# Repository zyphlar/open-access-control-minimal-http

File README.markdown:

Open Access Control - HTTP Minimal Edition
======================================
AKA Open Access Control Interlock
---------------------------------

This is a stripped-down version of the 23b hackerspace's Open Access Control system, intended for embedded use with an RFID reader and Ethernet shield for authenticating Wiegand RFID cards with a webservice. Please see http://code.google.com/p/open-access-control/ for the main/full version.

For more info, contact @willbradley on Twitter.

Structure
---------

* This folder
  * Open Access Control folder
    * Open Access Control.ino (Arduino code -- open from the Arduino IDE.)
  * libraries folder (copy the contents of this folder to your Arduino program's libraries folder and restart the Arduino program.)
    * ShiftLCD folder
      * keywords.txt
      * ShiftLCD.cpp
      * ShiftLCD.h
    * PCATTACH folder
      * keywords.txt
      * PCATTACH.cpp
      * PCATTACH.h
    * Wiegand26 folder
      * keywords.txt
      * WIEGAND26.cpp
      * WIEGAND26.h
  * hardware folder
    * open-access-interlock.brd

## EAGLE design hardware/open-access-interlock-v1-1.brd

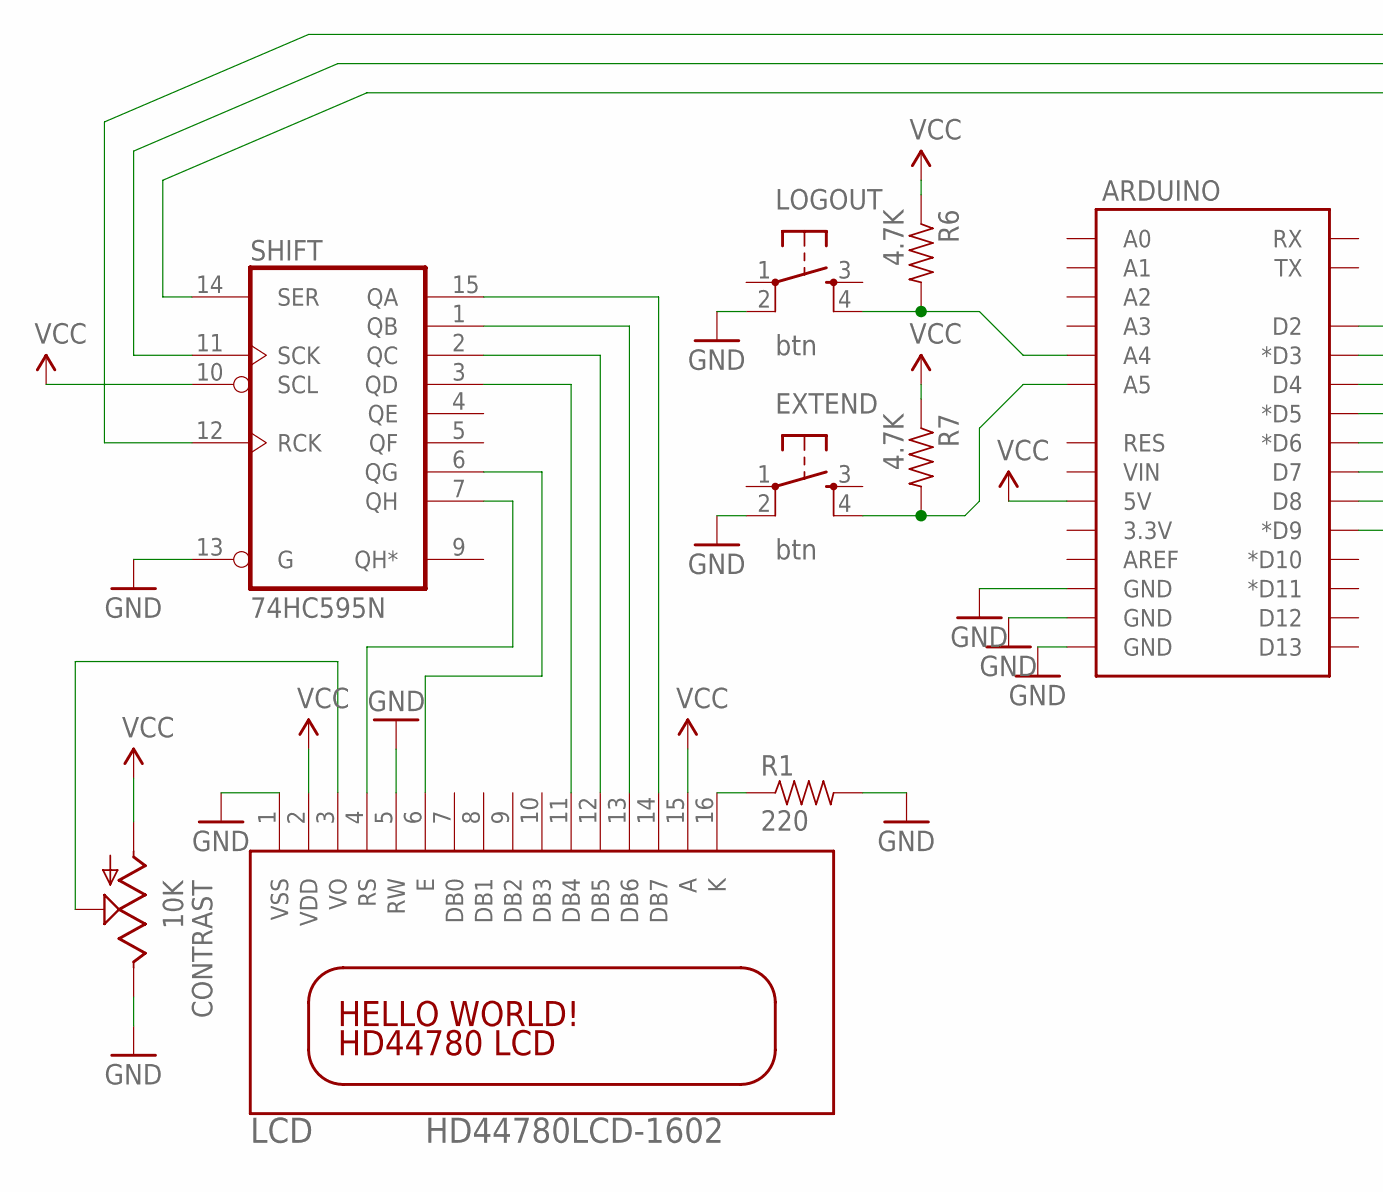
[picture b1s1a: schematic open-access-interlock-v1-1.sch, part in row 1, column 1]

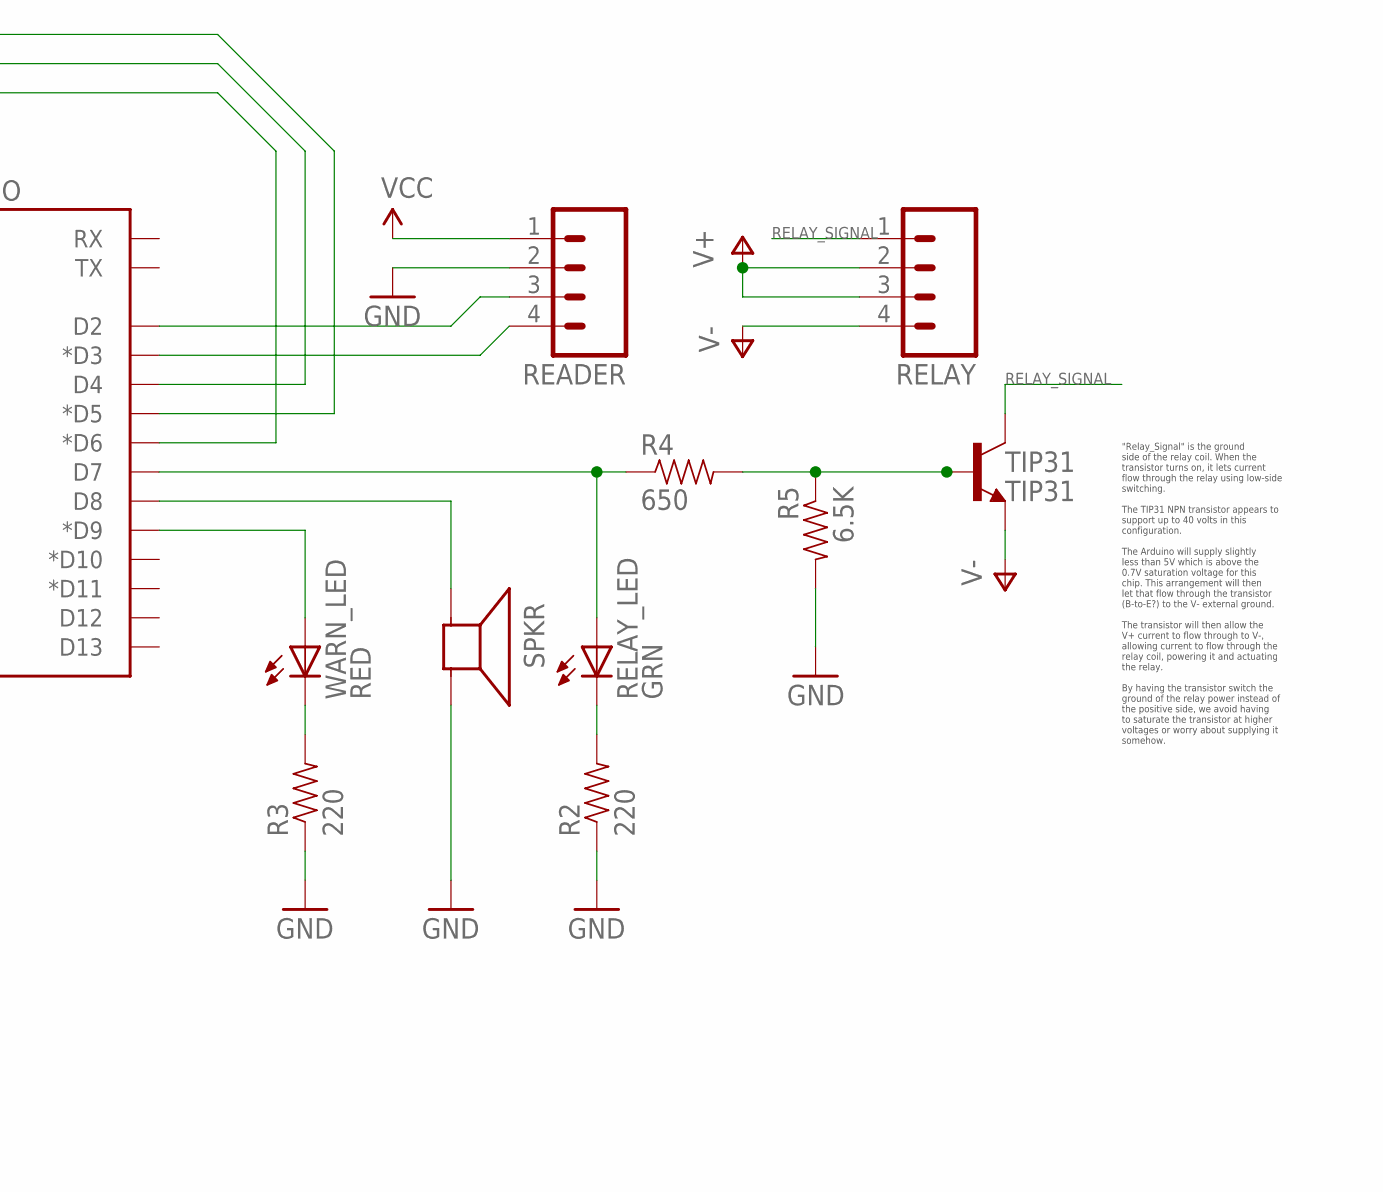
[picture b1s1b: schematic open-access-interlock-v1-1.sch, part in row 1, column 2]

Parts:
ARDUINO: ARDUINO_SHIELDNO_SILK; DUEMILANOVE_VIAS
CONTRAST: 10K; RS3
EXTEND: btn; TACTILE-PTH
LCD: HD44780LCD-1602; LCD1602
LOGOUT: btn; TACTILE-PTH
R1, R2, R3: 220; AXIAL-0.3
R4: 650; AXIAL-0.3
R5: 6.5K; AXIAL-0.3
R6, R7: 4.7K; AXIAL-0.3
READER: M04SCREW; SCREWTERMINAL-3.5MM-4
RELAY: M04SCREW; SCREWTERMINAL-3.5MM-4
RELAY_LED: GRN; LED5MM
SHIFT: 74HC595N; DIL16
SPKR: SPEAKER/PS12; PS12
TIP31: TIP31; TO220
WARN_LED: RED; LED5MM

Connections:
GND: ARDUINO.GND@0 (GND), ARDUINO.GND@1 (GND), ARDUINO.GND@2 (GND), CONTRAST.E, EXTEND.2, LCD.1 (VSS), LCD.5 (RW), LOGOUT.2, R1.P$2 (2), R2.P$1 (1), R3.P$1 (1), R5.P$2 (2), READER.2, SHIFT.8 (GND), SHIFT.13 (G), SPKR.P$2 (-)
unnamed: ARDUINO.D2, READER.3
unnamed: ARDUINO.D3 (*D3), READER.4
unnamed: LCD.13 (DB6), SHIFT.1 (QB)
unnamed: LCD.12 (DB5), SHIFT.2 (QC)
unnamed: ARDUINO.D6 (*D6), SHIFT.14 (SER)
unnamed: ARDUINO.D5 (*D5), SHIFT.12 (RCK)
unnamed: ARDUINO.D4, SHIFT.11 (SCK)
unnamed: ARDUINO.D7, R4.P$1 (1), RELAY_LED.A
unnamed: ARDUINO.D9 (*D9), WARN_LED.A
unnamed: ARDUINO.D8, SPKR.P$1 (+)
unnamed: LCD.6 (E), SHIFT.6 (QG)
unnamed: LCD.11 (DB4), SHIFT.3 (QD)
unnamed: ARDUINO.A4, LOGOUT.4, R6.P$2 (2)
unnamed: ARDUINO.A5, EXTEND.4, R7.P$2 (2)
unnamed: R2.P$2 (2), RELAY_LED.K (C)
unnamed: LCD.4 (RS), SHIFT.7 (QH)
unnamed: CONTRAST.S, LCD.3 (VO)
unnamed: LCD.16 (K), R1.P$1 (1)
unnamed: LCD.14 (DB7), SHIFT.15 (QA)
unnamed: R4.P$2 (2), R5.P$1 (1), TIP31.1 (B)
unnamed: R3.P$2 (2), WARN_LED.K (C)
RELAY_SIGNAL: RELAY.1, TIP31.2 (C)
V+: RELAY.2, RELAY.3
V-: RELAY.4, TIP31.3 (E)
VCC: ARDUINO.5V, CONTRAST.A, LCD.2 (VDD), LCD.15 (A), R6.P$1 (1), R7.P$1 (1), READER.1, SHIFT.10 (SCL), SHIFT.16 (VCC)

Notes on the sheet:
"Relay_Signal" is the ground side of the relay coil. When the transistor turns on, it lets current flow through the relay using low-side switching. The TIP31 NPN transistor appears to support up to 40 volts in this configuration. The Arduino will supply slightly less than 5V which is above the 0.7V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

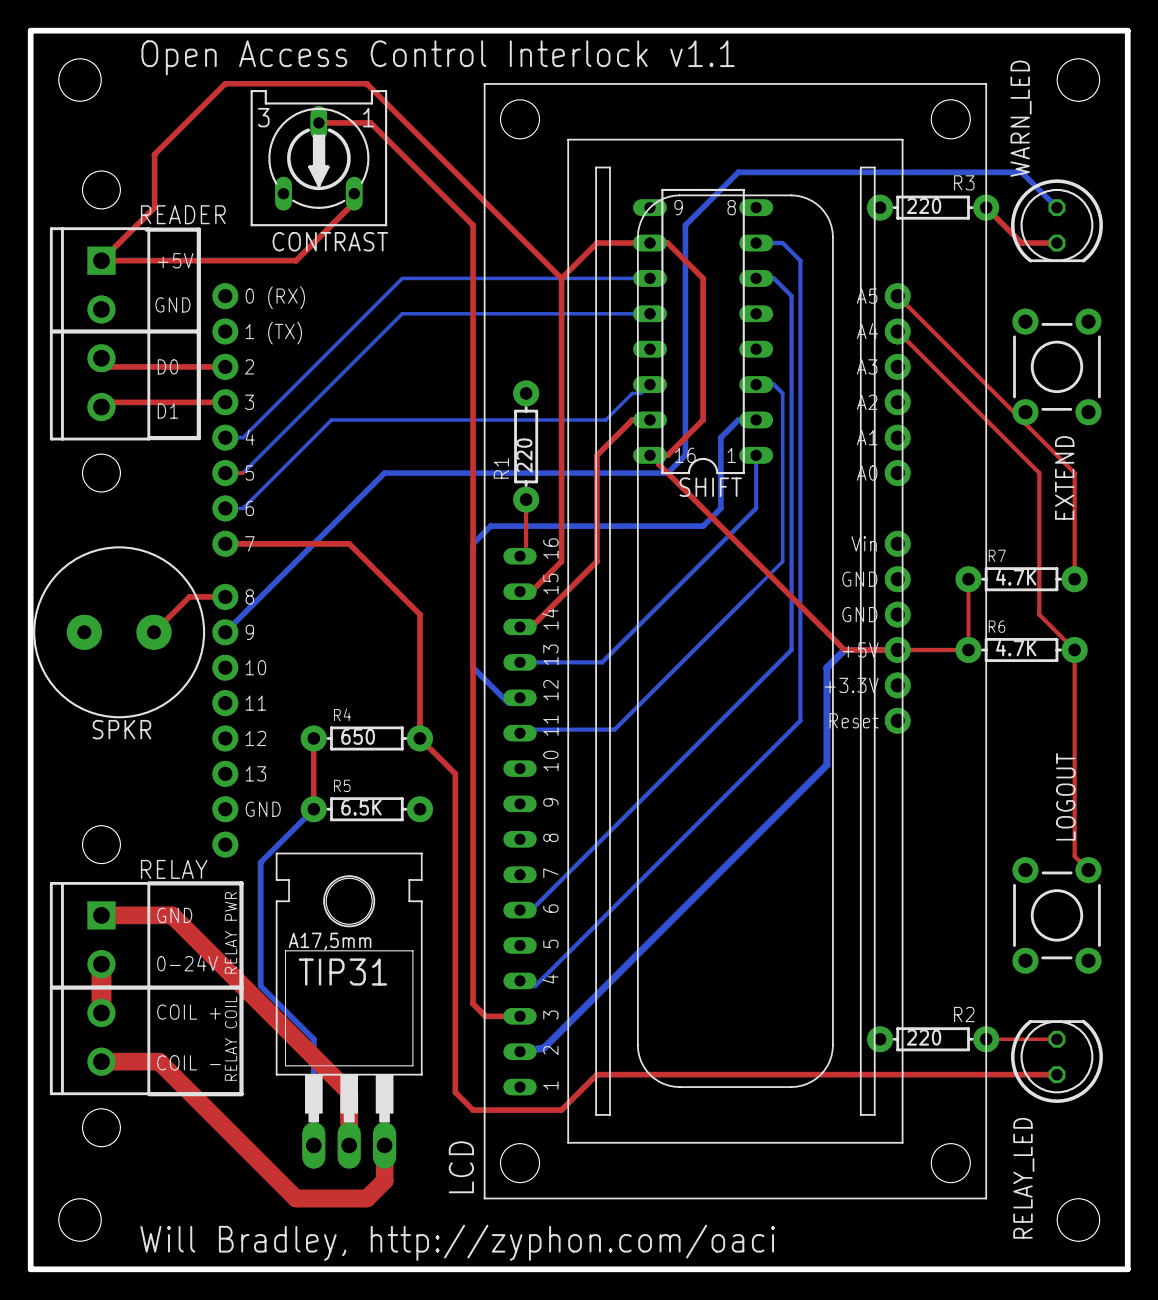
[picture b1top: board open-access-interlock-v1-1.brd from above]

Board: 2 copper layers, 78.7 x 88.9 mm, 23 parts (0 on the bottom side), 26 nets.

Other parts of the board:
U$2, U$3, U$4, U$5: STAND-OFF-TIGHT

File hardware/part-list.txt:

Partlist

Part      Value                 Device                Package               Library  Sheet

ARDUINO
Shield Headers                  Headers               1x6
Shield Headers                  Headers               1x6
Shield Headers                  Headers               1x8
Shield Headers                  Headers               1x8
SHIFT     74HC595N              Shift Reg             DIL16                 74xx-eu  1
SPKR      SPEAKER/PS12          SPEAKER/PS12          PS12                  adafruit 1
EXTEND    B3F-1060              Button                TACTILE-PTH           SparkFun 1
LOGOUT    B3F-1060              Button                TACTILE-PTH           SparkFun 1
LCD_HDR   1x16                  Header                1x16                  
LCD       HD44780LCD-1602       HD44780LCD-1602       LCD1602               adafruit 1
R1        220ohm                Resistor              AXIAL-0.3             SparkFun 1
R2        220ohm                Resistor              AXIAL-0.3             SparkFun 1
R3        220ohm                Resistor              AXIAL-0.3             SparkFun 1
CONTRAST  10K                   Trim Pot              5x5mm RS3             pot      1
RDR_DATA  SCREW                 Screw Term            SCREWTERMINAL-3.5MM-2 SparkFun 1
RDR_PWR   SCREW                 Screw Term            SCREWTERMINAL-3.5MM-2 SparkFun 1
RELAY     SCREW                 Screw Term            SCREWTERMINAL-3.5MM-2 SparkFun 1
RELAY_LED GRN                   LED 5MM               LED5MM                led      1
WARN_LED  RED                   LED 5MM               LED5MM                led      1

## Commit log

2011-11-28 Got HTTP polling working
2011-11-28 Removed everything but bare minimum functions
2011-11-28 Changed comments
2011-11-28 Edited readme, added libraries
2011-11-28 Got timer working
2011-11-28 Cleanup
2011-11-28 Pre-LCD
2011-11-28 Adding shift register LCD
2011-11-30 Got shift LCD working
2011-11-30 Updated readme; removed shiftlcd examples
2011-11-30 Added extend button
2011-11-30 Logout button working
2011-11-30 Adding hardware
2011-12-03 Made extend button able to extend past 30 minutes
2011-12-03 Revert "Adding hardware"
    This reverts commit f4d6aa5d7036346dabfb8877d4a0cfdd3cbdc8cb.
2011-12-03 Added alarms (buzzer and led)
2011-12-03 Revert "Revert "Adding hardware""
    This reverts commit c0f7f7396359c05a34af1b3f2b47c57ebe1d9022.
2011-12-03 Whups, last one was bad. This one is good.
2011-12-03 Added hardware to readme
2011-12-03 Fixed stray lines and comments
2011-12-03 Finished testing, changed debounce
2011-12-03 Added more hardware
2011-12-07 More hardware work
2011-12-07 Switched to 16x1 lcd header instead of 7x2
2011-12-07 Routed the new lcd
2011-12-07 Updated board layout, widths, speaker component
2011-12-07 Changed pot to 5mm x 5mm footprint
2011-12-21 Fixing 465-456 pin error, pin6 mishap, adding transistor/resistors, moving lcd lower
2014-02-23 Readme update, relay files
2014-02-23 Arduino 1.0 compat, minor tweaks, fixing LCD
2014-02-23 Library Arduino 1.0 compatibility
2014-02-23 Comment updates
2014-02-23 Added pullup resistors, moved LCD slightly
2014-02-23 Updated with better screw terminals
2014-02-23 Final tweaks for terminals and labels
2014-02-23 Removing old files
2014-02-24 Fixing transistor/relay stuff
2014-02-24 Ripping up terminal blocks
2014-02-24 Mounting holes, routing tweaks
2014-02-24 Seedstudio DRU rules
2014-02-25 Updating board/schematic png
2021-09-28 Rename and add photos
2021-09-28 photo display

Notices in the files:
parts and their libraries:
SparkFun-Connectors: Licensing: Creative Commons ShareAlike 4.0 International - https://creativecommons.org/licenses/by-sa/4.0
